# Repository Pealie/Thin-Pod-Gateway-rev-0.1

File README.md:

# Thin-Pod Gateway rev 0.1

<p align="left">
  
</p>
<p align="left">
  <strong>OSHWA Certified Open Source Hardware · UK000092</strong><br>
  Certified 16 July 2026 · <a href="https://certification.oshwa.org/uk000092.html">View certification record</a>
</p>

**Open-hardware carrier PCB for Thin-Pod UWB telemetry, host supervision and onward-networking experiments**

## Status at 16 July 2026

Thin-Pod Gateway rev 0.1 is certified by the Open Source Hardware Association under UID [`UK000092`](https://certification.oshwa.org/uk000092.html). The certified public baseline is the `v0.1` release, with post-certification status and directory references maintained on `main`.

The manufactured `rev 0.1f` carrier board has completed stable powered bring-up with the STM32 NUCLEO-N657X0-Q and Gateway-side DWM3001-CDK. The repository records:

- verified 5 V and 3.3 V distribution and common-ground continuity;
- corrected marginal DWM header solder joints affecting ground and RESET;
- valid RESET and READY rail levels;
- repeatable bidirectional NUCLEO-to-DWM `TPHIP GET_CAPABILITIES` exchange;
- physical DW3110 identity and initialisation on Gateway and Node DWM3001-CDKs;
- a matched 20-frame Gateway-to-Node UWB exchange;
- published KiCad project, schematic and PCB source for revision `0.1`;
- published Gerber, drill and fabrication ZIP outputs;
- clean schematic ERC and PCB DRC reports;
- recorded Gerber and drill inspection;
- recorded symbol and footprint provenance;
- a reconciled design-basis BOM with builder-selected compatible assembly hardware.

## Relationship to the certified Thin-Pod node

The companion [`Pealie/Thin-Pod-rev0.1`](https://github.com/Pealie/Thin-Pod-rev0.1) sensor-node carrier PCB is separately certified as OSHWA Open Source Hardware, UID [`UK000091`](https://certification.oshwa.org/uk000091.html), certified 28 May 2026.

The two certifications describe distinct hardware artefacts:

| Hardware artefact | OSHWA UID | Certification date |
|---|---|---|
| Thin-Pod rev 0.1 sensor-node carrier PCB | [`UK000091`](https://certification.oshwa.org/uk000091.html) | 28 May 2026 |
| Thin-Pod Gateway rev 0.1 carrier PCB | [`UK000092`](https://certification.oshwa.org/uk000092.html) | 16 July 2026 |

The node UID applies only to the sensor-node carrier PCB. The Gateway UID applies only to the Gateway carrier PCB and its declared certification package.

## Hardware scope

Thin-Pod Gateway rev 0.1 is a two-layer carrier PCB connecting:

| Reference | Module | Role |
|---|---|---|
| `U1` | STMicroelectronics `NUCLEO-N657X0-Q` | Main host and prospective analysis supervisor |
| `U2` | Qorvo `DWM3001-CDK` | Gateway-side UWB subsystem |
| `U3` | Seeed Studio `XIAO ESP32-C6` | Optional onward-networking subsystem |

The creator-controlled open-hardware contribution is the carrier PCB: power distribution, local decoupling, pull-ups, module interfaces, SPI/control routing, test access, mounting geometry, editable source and derived fabrication outputs.

The commercial modules remain third-party products whose internal designs are outside the Gateway open-hardware claim.

## Verified evidence

| Milestone | Result | Evidence |
|---|---|---|
| Stable carrier-board bring-up | PASS | [`docs/bringup/Gateway_rev0_1_Hardware_Bringup_Note.md`](docs/bringup/Gateway_rev0_1_Hardware_Bringup_Note.md) |
| NUCLEO-to-DWM physical host interface | PASS | [`docs/firmware/TPHIP_GET_CAPABILITIES_Physical_Validation.md`](docs/firmware/TPHIP_GET_CAPABILITIES_Physical_Validation.md) |
| DW3110 identity and initialisation | PASS | [`docs/validation/DW3110_Physical_Identity_Initialisation_Validation.md`](docs/validation/DW3110_Physical_Identity_Initialisation_Validation.md) |
| Matched 20-frame one-way RF exchange | PASS | [`docs/validation/DW3110_One_Way_RF_Exchange_Validation.md`](docs/validation/DW3110_One_Way_RF_Exchange_Validation.md) |
| Native KiCad source | PUBLISHED | [`hardware/source/README.md`](hardware/source/README.md) |
| Fabrication package and hashes | PUBLISHED | [`hardware/fabrication/RELEASE-MANIFEST.md`](hardware/fabrication/RELEASE-MANIFEST.md) |
| Schematic ERC | PASS | [`docs/validation/cad/rev0.1/Thin-Pod_Gateway_rev0.1_ERC.rpt`](docs/validation/cad/rev0.1/Thin-Pod_Gateway_rev0.1_ERC.rpt) |
| PCB DRC | PASS | [`docs/validation/cad/rev0.1/Thin-Pod_Gateway_rev0.1_DRC.rpt`](docs/validation/cad/rev0.1/Thin-Pod_Gateway_rev0.1_DRC.rpt) |
| Gerber and drill inspection | PASS | [`docs/validation/cad/rev0.1/Gerber_Drill_Inspection_Record.md`](docs/validation/cad/rev0.1/Gerber_Drill_Inspection_Record.md) |
| Symbol and footprint provenance | RECORDED | [`docs/footprint-provenance.md`](docs/footprint-provenance.md) |
| Assembly BOM | RECONCILED | [`hardware/bom/Thin-Pod_Gateway_rev0.1_BOM.md`](hardware/bom/Thin-Pod_Gateway_rev0.1_BOM.md) |

## Design and fabrication identity

The manufactured board may carry `rev 0.1f`. This is retained as the physical fabrication-build identity within the certified Thin-Pod Gateway rev 0.1 release record.

Published native source:

```text
hardware/source/kicad/rev0.1/
```

Published manufacturing outputs:

```text
hardware/fabrication/rev0.1/
```

The release Gerber job records project revision `0.1`. The regenerated outputs preserve the intended electrical connectivity, board outline, mounting geometry, module-interface positions, test-point arrangement and layer content of the manufactured rev 0.1f carrier.

## Assembly interface treatment

Builder-selected pin headers and/or socket strips compatible with the NUCLEO-N657X0-Q ST Morpho interfaces, DWM3001-CDK J10 interface, and optional XIAO ESP32-C6 carrier footprint are suitable for assembly. Header brand, plating, socket style and standoff selection are assembly choices outside the carrier-PCB certification scope.

## Licences

| Material | Licence |
|---|---|
| Creator-designed hardware source and derived fabrication outputs | `CERN-OHL-W-2.0` |
| Project-authored firmware, scripts and software examples | `MIT` |
| Creator-authored documentation and owned images | `CC-BY-4.0` |
| Third-party modules, software and CAD | Original applicable terms |

These are the licence selections recorded for OSHWA certification UID `UK000092`.

See [`LICENSE.md`](LICENSE.md), [`LICENSE-HARDWARE.md`](LICENSE-HARDWARE.md), [`LICENSE-SOFTWARE.md`](LICENSE-SOFTWARE.md), [`LICENSE-DOCUMENTATION.md`](LICENSE-DOCUMENTATION.md), [`THIRD_PARTY_NOTICES.md`](THIRD_PARTY_NOTICES.md) and [`docs/footprint-provenance.md`](docs/footprint-provenance.md).

## OSHWA certification record

| Item | Record |
|---|---|
| Project | Thin-Pod Gateway |
| Hardware release | rev 0.1 |
| OSHWA UID | [`UK000092`](https://certification.oshwa.org/uk000092.html) |
| Certification date | 16 July 2026 |
| Canonical release tag | `v0.1` |
| Public application record | [`oshwa/application-record.md`](oshwa/application-record.md) |
| Certification scope | [`docs/certification-scope.md`](docs/certification-scope.md) |
| Certification completion checklist | [`docs/oshwa/Gateway_OSHWA_Preparation_Checklist.md`](docs/oshwa/Gateway_OSHWA_Preparation_Checklist.md) |

The OSHWA certification confirms the declared open-source hardware, software and documentation licensing position. It does not constitute EMC, radio, electrical-safety, CE, UKCA, industrial-performance or product-safety approval.

## Current limitations

The release does not claim Node-to-Gateway vibration-window transport, ranging, field-qualified RF performance, calibrated transmit power, antenna/coexistence performance, authenticated radio records, secure boot enforcement, production OTA, Gateway DSP/TinyML performance, EMC, radio, electrical-safety, CE or UKCA compliance.

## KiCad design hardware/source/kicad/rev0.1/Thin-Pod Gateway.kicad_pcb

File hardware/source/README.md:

# Editable hardware source

This directory contains the preferred modifiable source for Thin-Pod Gateway rev 0.1.

## Published KiCad project

The release source is stored at:

```text
hardware/source/kicad/rev0.1/
├── Thin-Pod Gateway.kicad_pro
├── Thin-Pod Gateway.kicad_sch
└── Thin-Pod Gateway.kicad_pcb
```

The schematic and PCB title blocks identify the design revision as `0.1`. The KiCad project and PCB fabrication-output paths use the repository-relative location:

```text
../../../fabrication/rev0.1/
```

This removes the private Windows/OneDrive path that was present in the working project before publication. No schematic connectivity, component placement, routing or board geometry was intentionally changed by that portability correction.

## Source status

The native KiCad source and corresponding Gerber/drill release package were committed on 13 July 2026. The earlier missing-source publication gate is therefore cleared.

The remaining release-verification work is:

1. open the project in a clean KiCad 10 environment;
2. confirm that no unavailable private symbol or footprint library is required;
3. run schematic ERC and PCB DRC;
4. inspect the generated Gerbers and drill data in a Gerber viewer;
5. record symbol and footprint provenance;
6. reconcile the fitted BOM and module-header/socket choices;
7. freeze the validated source and fabrication package under a public release tag.

The editable KiCad project is the normative design source. Gerbers, drill data and the fabrication ZIP are derived convenience outputs.

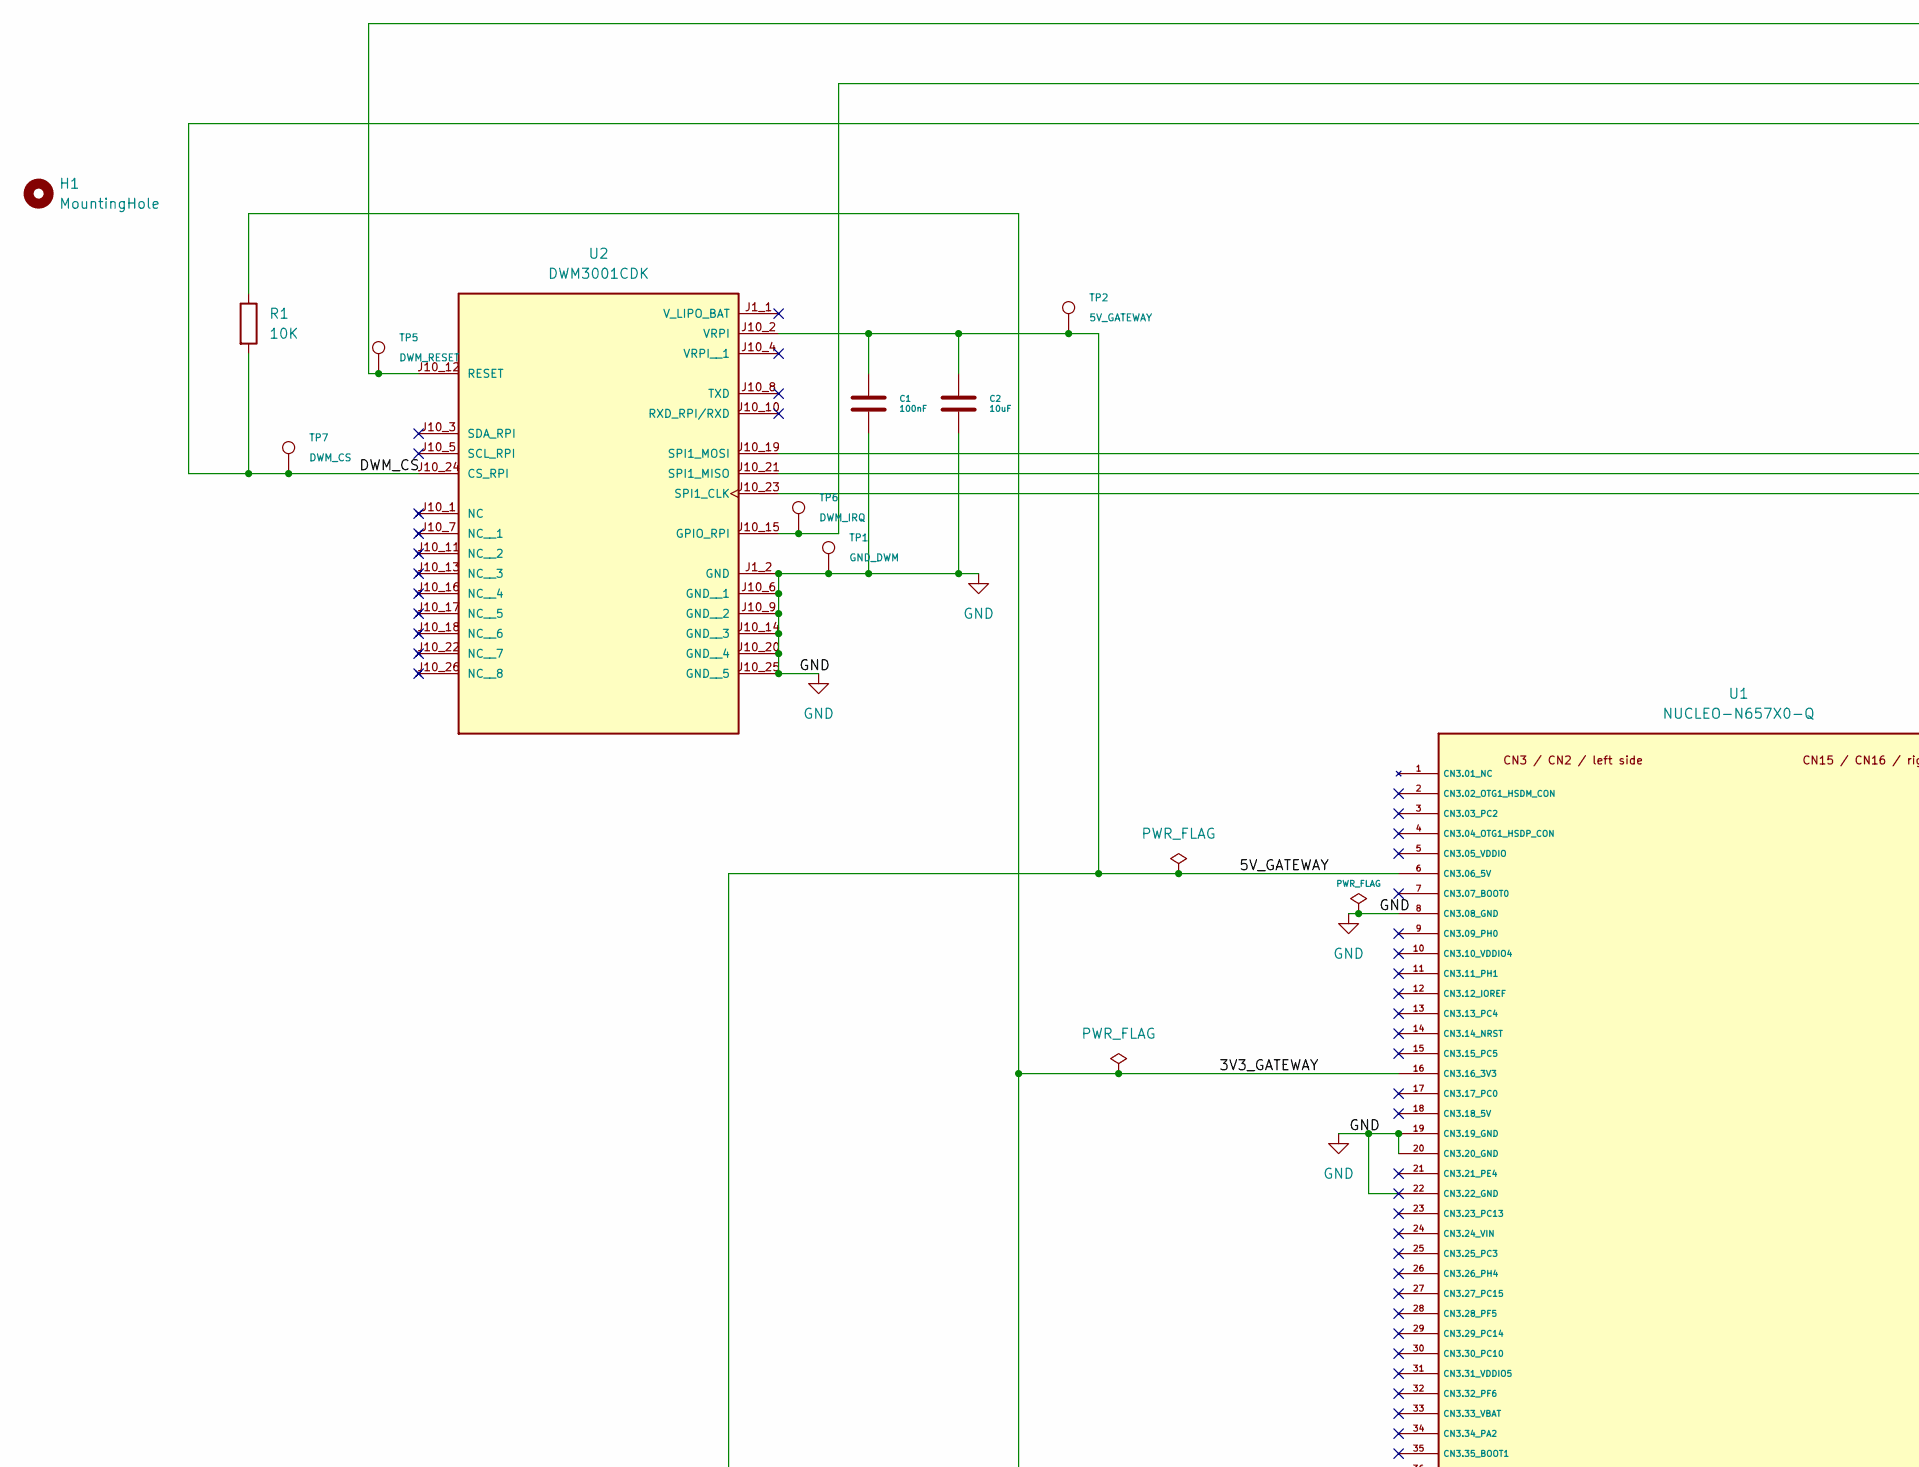
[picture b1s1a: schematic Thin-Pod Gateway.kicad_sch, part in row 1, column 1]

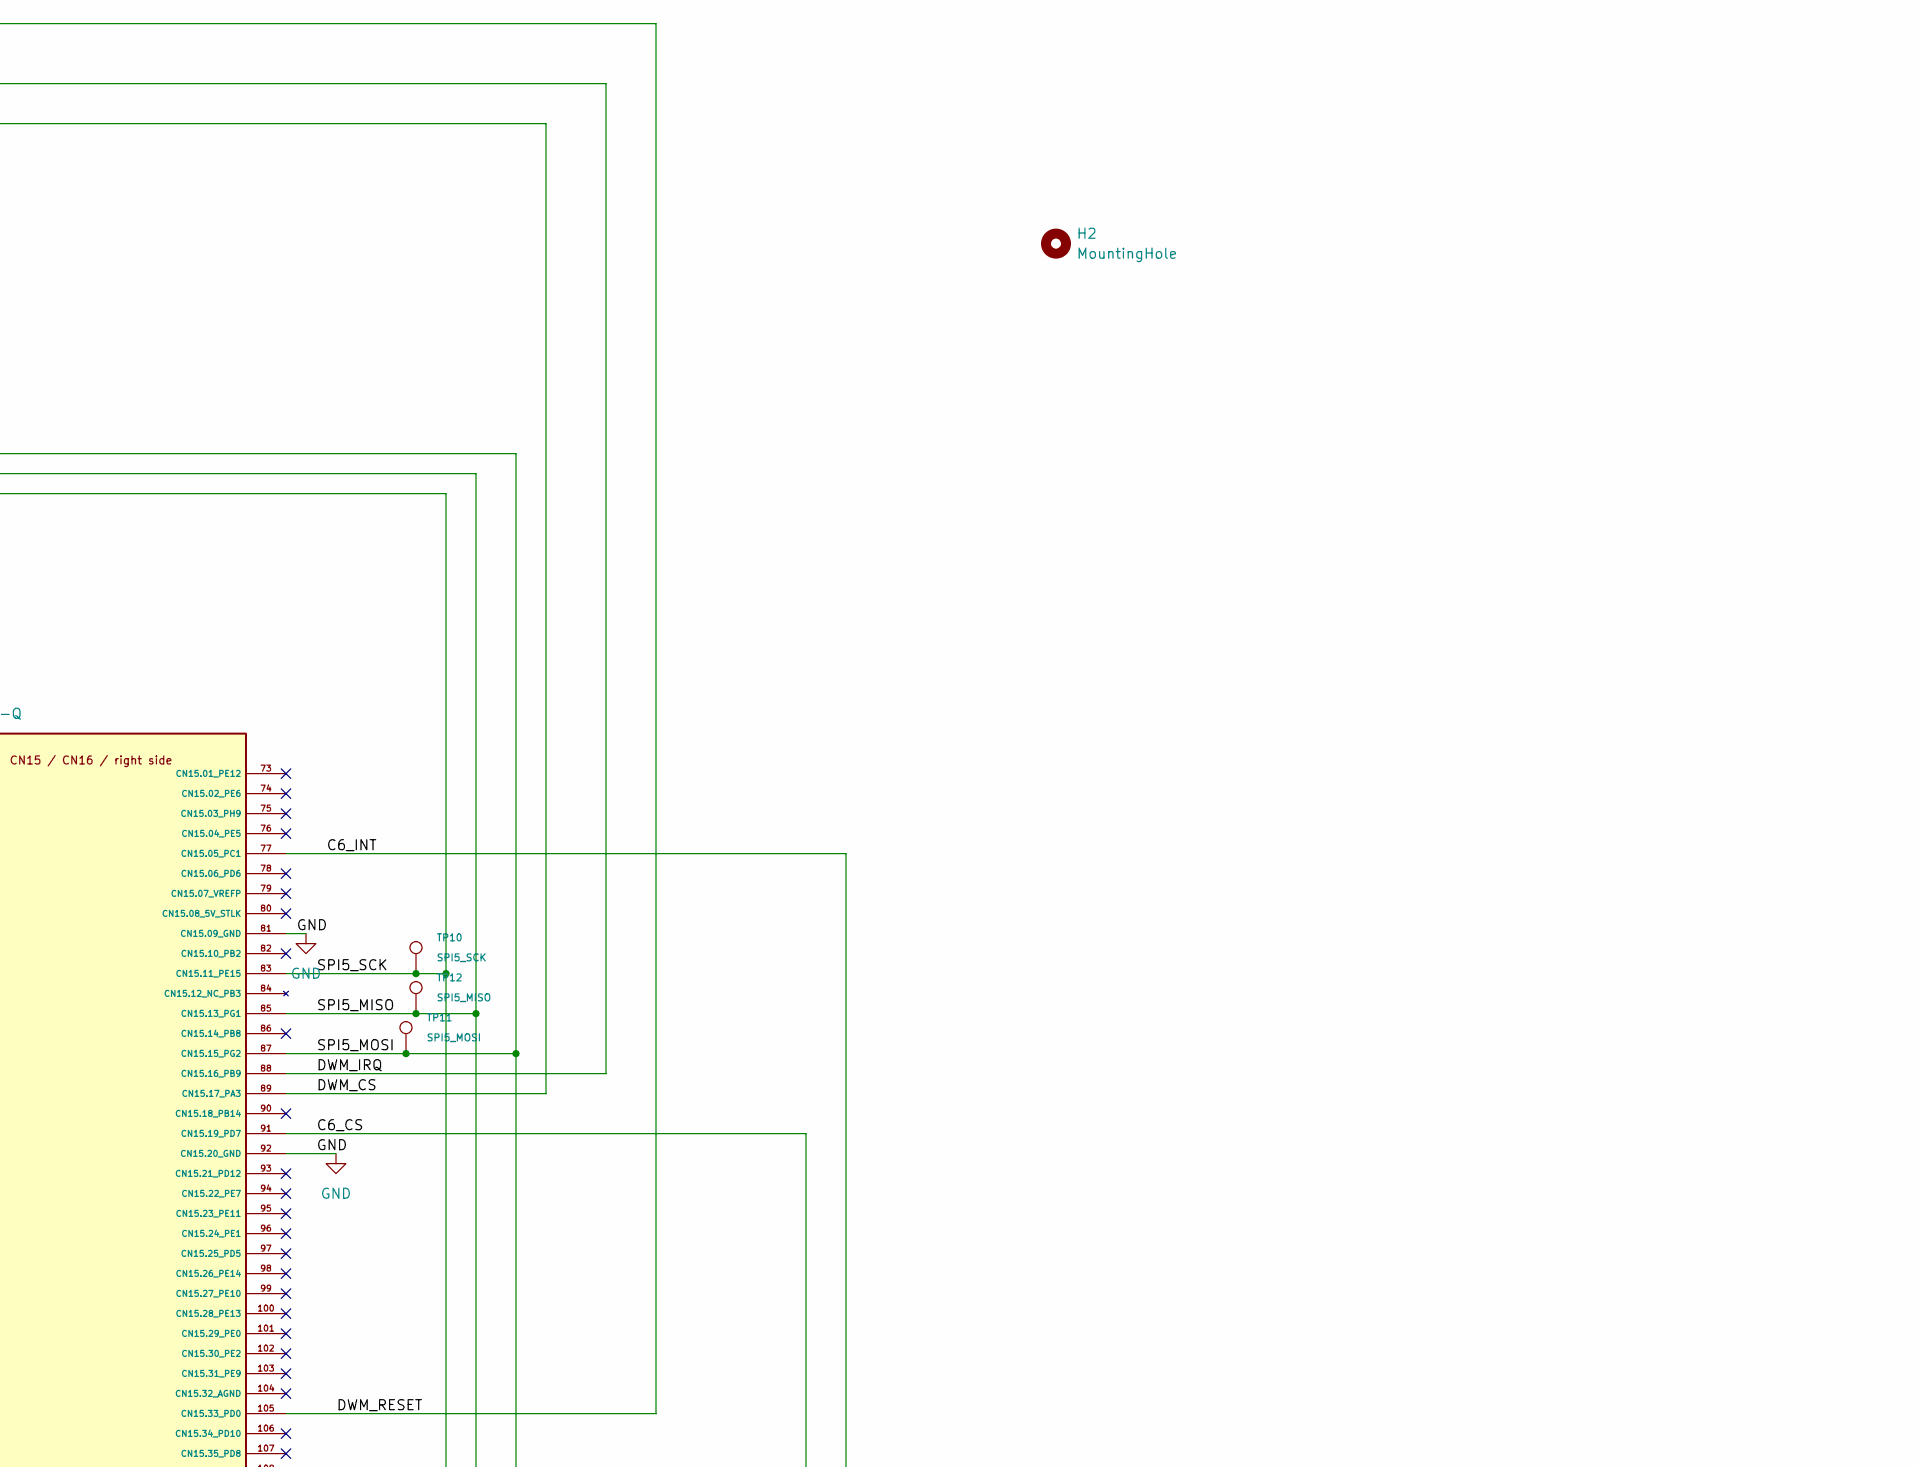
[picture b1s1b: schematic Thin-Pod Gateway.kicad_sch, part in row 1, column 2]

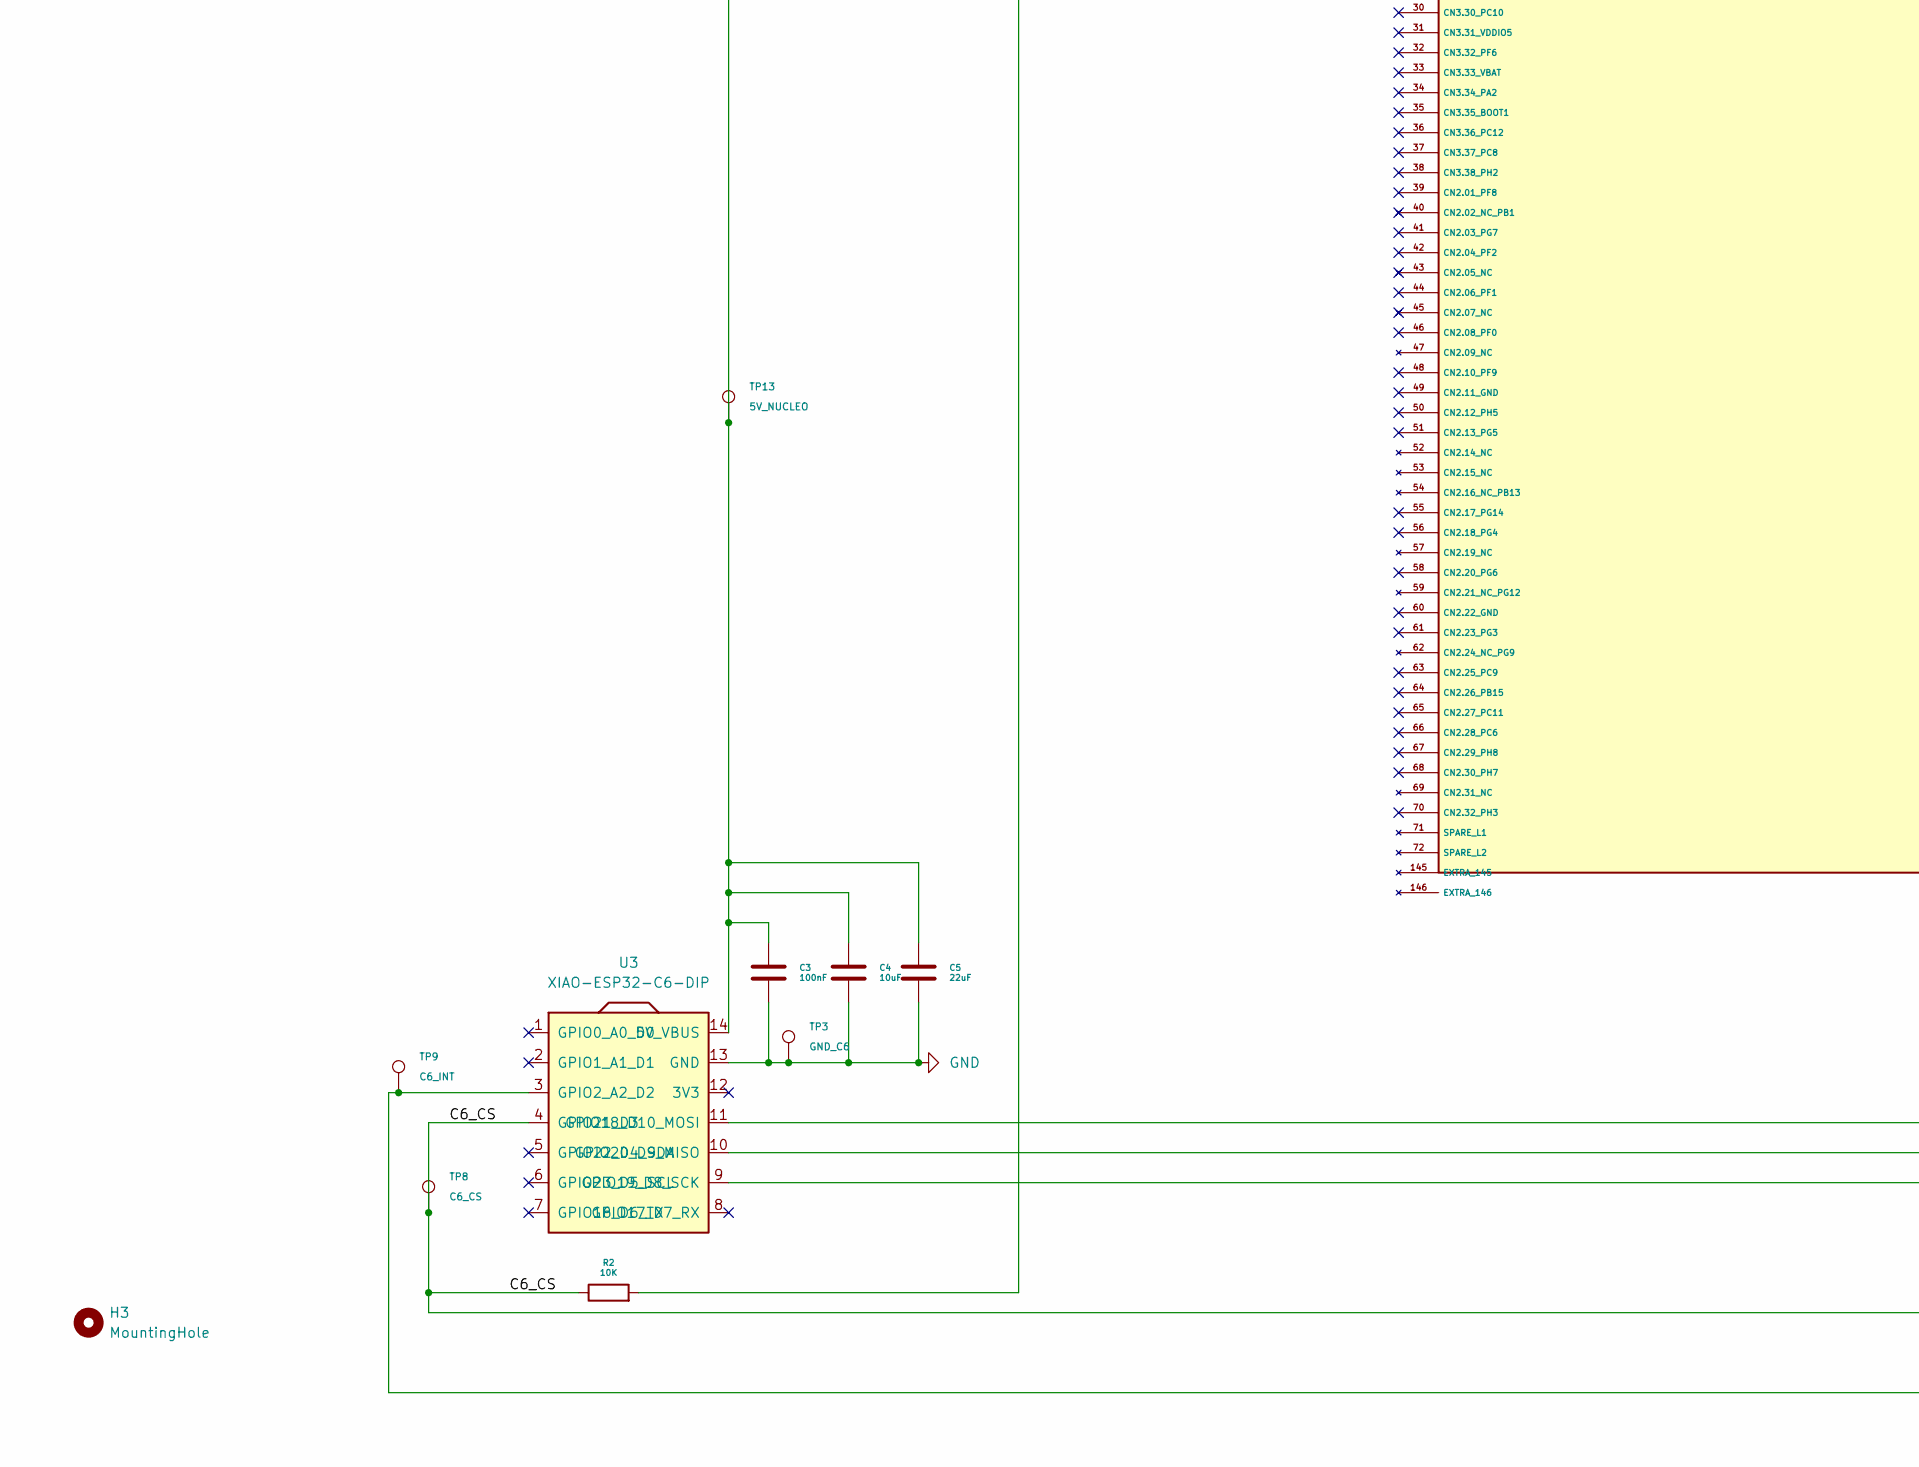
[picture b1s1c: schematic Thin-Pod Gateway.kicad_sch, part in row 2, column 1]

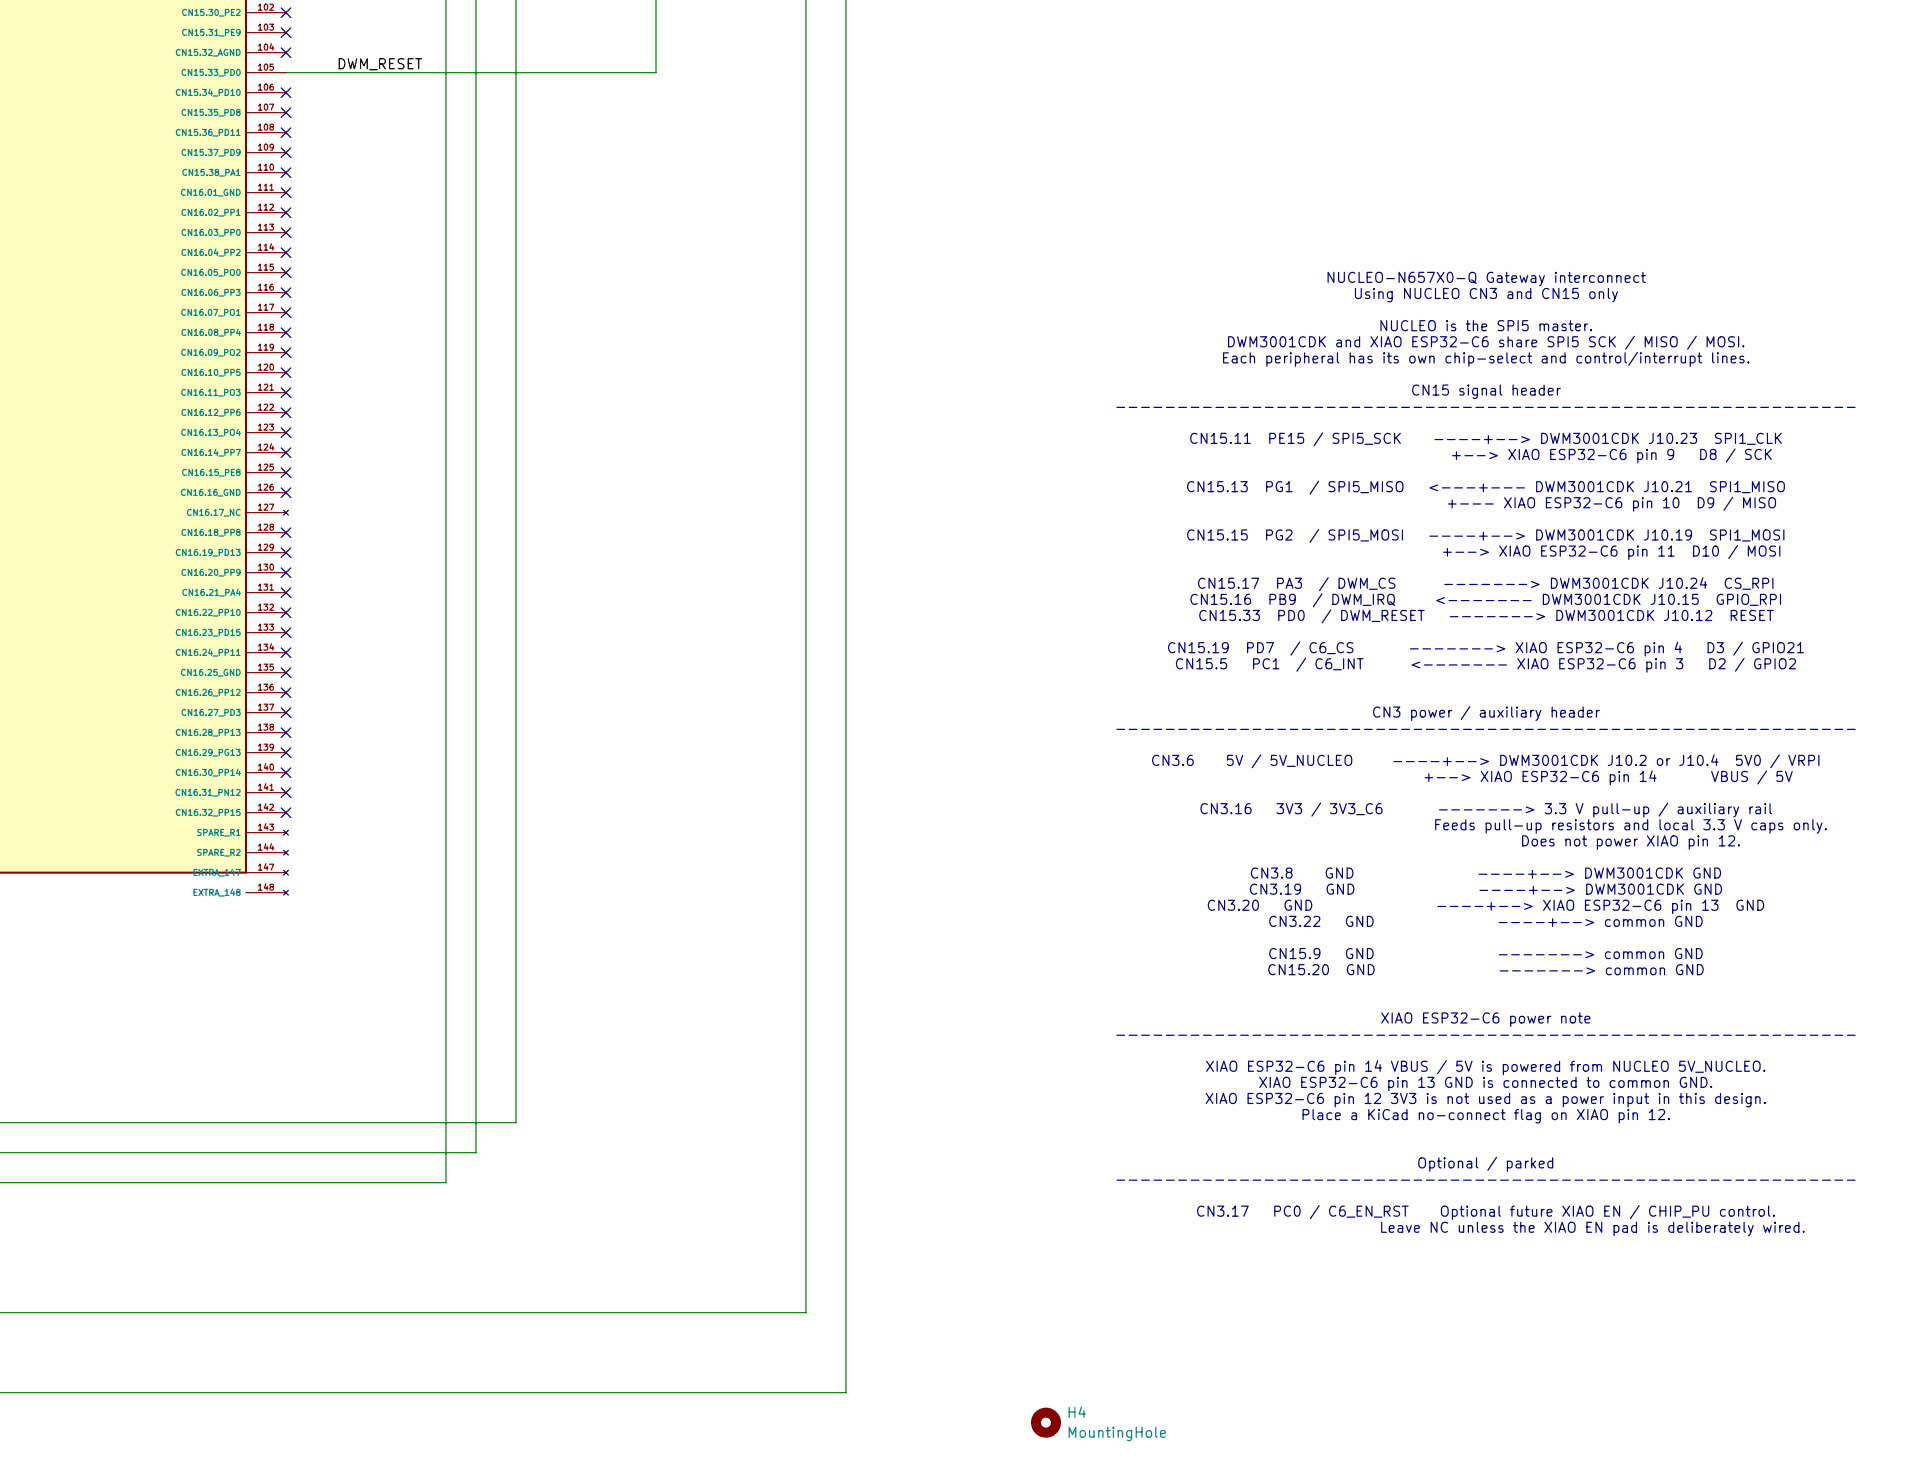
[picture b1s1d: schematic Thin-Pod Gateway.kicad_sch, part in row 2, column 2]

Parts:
C1, C3: 100nF; C_Disc_D5.0mm_W2.5mm_P5.00mm
C2, C4: 10uF; C_Disc_D5.0mm_W2.5mm_P5.00mm
C5: 22uF; C_Disc_D5.0mm_W2.5mm_P5.00mm
H1, H2, H3, H4: MountingHole; MountingHole_3.2mm_M3
R1, R2: 10K; R_Axial_DIN0207_L6.3mm_D2.5mm_P7.62mm_Horizontal
TP1: GND_DWM; TestPoint_THTPad_1.5x1.5mm_Drill0.7mm
TP2: 5V_GATEWAY; TestPoint_THTPad_1.5x1.5mm_Drill0.7mm
TP3: GND_C6; TestPoint_THTPad_1.5x1.5mm_Drill0.7mm
TP5: DWM_RESET; TestPoint_THTPad_1.5x1.5mm_Drill0.7mm
TP6: DWM_IRQ; TestPoint_THTPad_1.5x1.5mm_Drill0.7mm
TP7: DWM_CS; TestPoint_THTPad_1.5x1.5mm_Drill0.7mm
TP8: C6_CS; TestPoint_THTPad_1.5x1.5mm_Drill0.7mm
TP9: C6_INT; TestPoint_THTPad_1.5x1.5mm_Drill0.7mm
TP10: SPI5_SCK; TestPoint_THTPad_2.0x2.0mm_Drill1.0mm
TP11: SPI5_MOSI; TestPoint_THTPad_2.0x2.0mm_Drill1.0mm
TP12: SPI5_MISO; TestPoint_THTPad_2.0x2.0mm_Drill1.0mm
TP13: 5V_NUCLEO; TestPoint_THTPad_1.5x1.5mm_Drill0.7mm
U1: NUCLEO-N657X0-Q; NUCLEO-N657X0-Q_Nucleo144_STMorpho_STLink_MountingHoles
U2: DWM3001CDK; MODULE_DWM3001CDK; PARTREV B
U3: XIAO-ESP32-C6-DIP

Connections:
/3V3_GATEWAY: R1.1, R2.2, U1.16 (CN3.16_3V3); also elsewhere on the board
/5V_GATEWAY: C1.1, C2.1, C3.1, C4.1, C5.1, TP2.1 (1_1), TP13.1 (1_1), U1.6 (CN3.06_5V), U2.J10_2 (VRPI), U3.14 (5V_VBUS)
/C6_CS: R2.1, TP8.1 (1_1), U1.91 (CN15.19_PD7), U3.4 (GPIO21_D3)
/C6_INT: TP9.1 (1_1), U1.77 (CN15.05_PC1), U3.3 (GPIO2_A2_D2)
/DWM_CS: R1.2, TP7.1 (1_1), U1.89 (CN15.17_PA3), U2.J10_24 (CS_RPI)
/DWM_IRQ: TP6.1 (1_1), U1.88 (CN15.16_PB9), U2.J10_15 (GPIO_RPI)
/DWM_RESET: TP5.1 (1_1), U1.105 (CN15.33_PD0), U2.J10_12 (RESET)
/SPI5_MISO: TP12.1 (1_1), U1.85 (CN15.13_PG1), U2.J10_21 (SPI1_MISO), U3.10 (GPIO20_D9_MISO)
/SPI5_MOSI: TP11.1 (1_1), U1.87 (CN15.15_PG2), U2.J10_19 (SPI1_MOSI), U3.11 (GPIO18_D10_MOSI)
/SPI5_SCK: TP10.1 (1_1), U1.83 (CN15.11_PE15), U2.J10_23 (SPI1_CLK), U3.9 (GPIO19_D8_SCK)
GND: C1.2, C2.2, C3.2, C4.2, C5.2, TP1.1 (1_1), TP3.1 (1_1), U1.1 (CN3.01_NC), U1.2 (CN3.02_OTG1_HSDM_CON), U1.8 (CN3.08_GND), U1.19 (CN3.19_GND), U1.20 (CN3.20_GND), U1.22 (CN3.22_GND), U1.71 (SPARE_L1), U1.72 (SPARE_L2), U1.73 (CN15.01_PE12), U1.74 (CN15.02_PE6), U1.81 (CN15.09_GND), U1.92 (CN15.20_GND), U1.143 (SPARE_R1), U1.144 (SPARE_R2), U2.J1_2 (GND), U2.J10_6 (GND__1), U2.J10_9 (GND__2), U2.J10_14 (GND__3), U2.J10_20 (GND__4), U2.J10_25 (GND__5), U3.13 (GND)

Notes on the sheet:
NUCLEO-N657X0-Q Gateway interconnect Using NUCLEO CN3 and CN15 only NUCLEO is the SPI5 master. DWM3001CDK and XIAO ESP32-C6 share SPI5 SCK / MISO / MOSI. Each peripheral has its own chip-select and control/interrupt lines. CN15 signal header ---------------------------------------------------------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

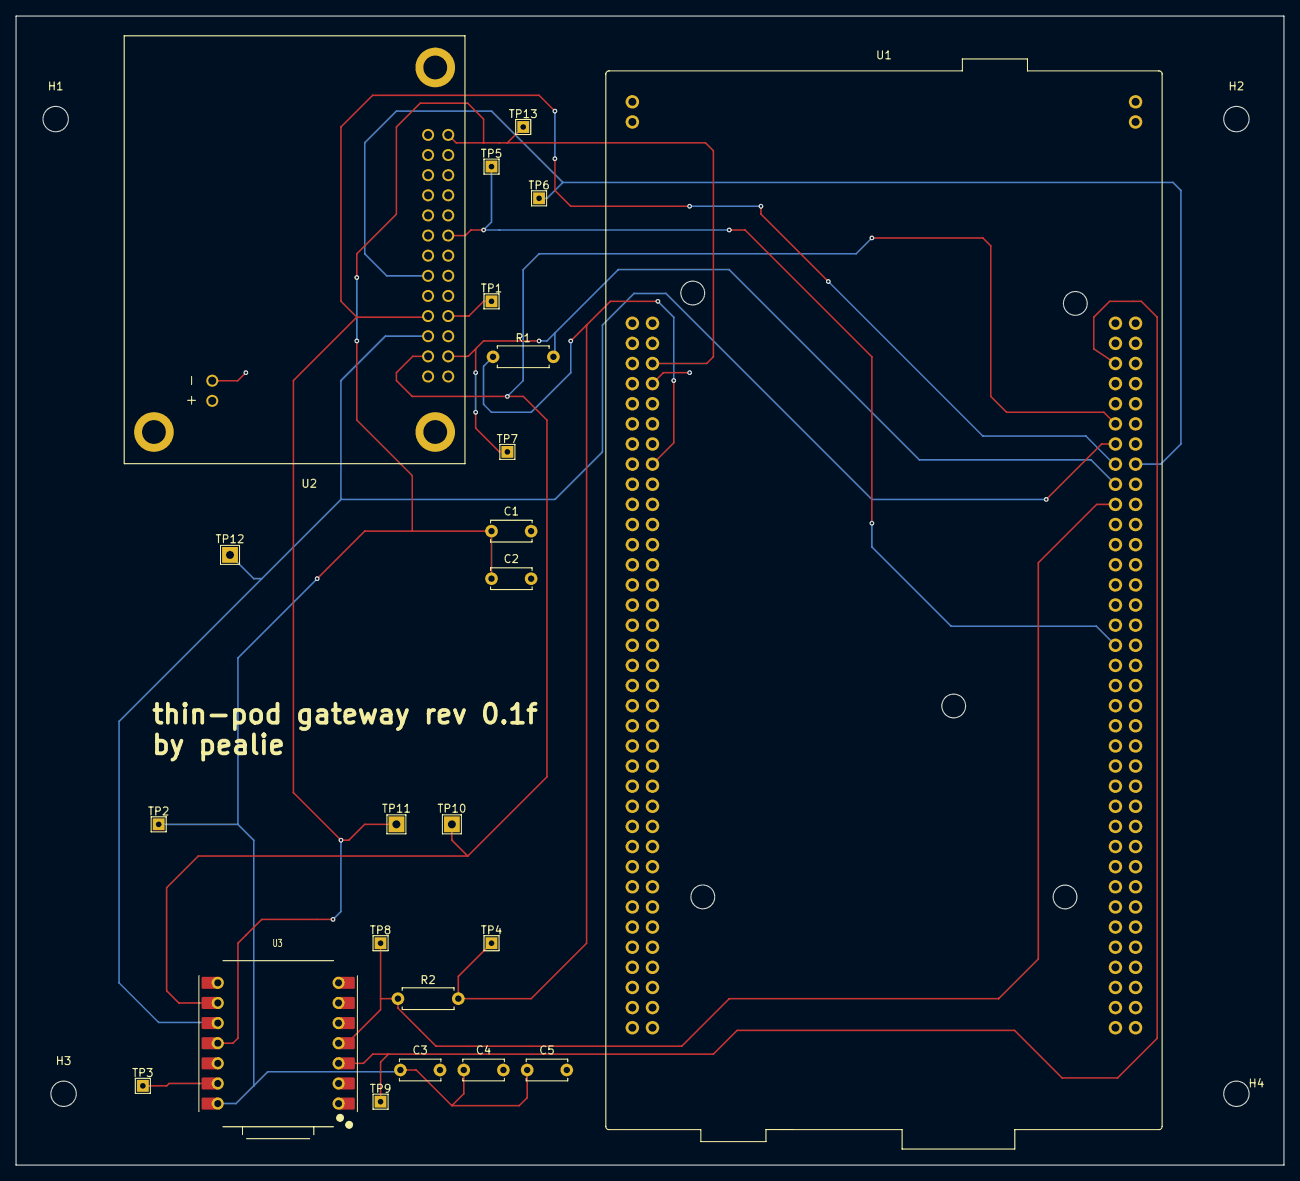
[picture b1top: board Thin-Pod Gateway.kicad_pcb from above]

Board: 2 copper layers, 160.0 x 145.0 mm, 27 parts (0 on the bottom side), 11 nets.

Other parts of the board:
TP4: 3V3_GATEWAY; TestPoint_THTPad_1.5x1.5mm_Drill0.7mm

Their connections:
/3V3_GATEWAY: TP4.1 (1_1); also elsewhere on the board

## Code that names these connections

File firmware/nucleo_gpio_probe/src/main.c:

#include <errno.h>
#include <stdint.h>

#include <zephyr/device.h>
#include <zephyr/drivers/gpio.h>
#include <zephyr/kernel.h>
#include <zephyr/sys/printk.h>

#define PROBE_SLEEP_MS 1000
#define TOGGLE_HOLD_MS 250

static const struct gpio_dt_spec dwm_reset =
	GPIO_DT_SPEC_GET(DT_ALIAS(dwm_reset), gpios);

static const struct gpio_dt_spec dwm_cs =
	GPIO_DT_SPEC_GET(DT_ALIAS(dwm_cs), gpios);

static const struct gpio_dt_spec dwm_irq =
	GPIO_DT_SPEC_GET(DT_ALIAS(dwm_irq), gpios);

static int check_gpio_ready(const struct gpio_dt_spec *spec, const char *name)
{
	if (!device_is_ready(spec->port)) {
		printk("ERROR: %s GPIO device not ready\n", name);
		return -ENODEV;
	}

	printk("%s ready: controller=%s pin=%u\n",
	       name, spec->port->name, spec->pin);

	return 0;
}

int main(void)
{
	int irq_level;
	uint32_t heartbeat = 0U;

	printk("\nThin-Pod Gateway rev0.1 NUCLEO GPIO probe\n");
	printk("Board: nucleo_n657x0_q\n");
	printk("Purpose: RESET / CS / IRQ pin-path confirmation only\n");
	printk("No SPI. No DW3110 register access. No UWB RF.\n\n");

	if (check_gpio_ready(&dwm_reset, "DWM_RESET / PD0") != 0) {
		return 0;
	}

	if (check_gpio_ready(&dwm_cs, "DWM_CS / PA3") != 0) {
		return 0;
	}

	if (check_gpio_ready(&dwm_irq, "DWM_IRQ / PB9") != 0) {
		return 0;
	}

	if (gpio_pin_configure_dt(&dwm_reset, GPIO_OUTPUT_LOW) != 0) {
		printk("ERROR: failed to configure DWM_RESET / PD0\n");
		return 0;
	}

	if (gpio_pin_configure_dt(&dwm_cs, GPIO_OUTPUT_LOW) != 0) {
		printk("ERROR: failed to configure DWM_CS / PA3\n");
		return 0;
	}

	if (gpio_pin_configure_dt(&dwm_irq, GPIO_INPUT) != 0) {
		printk("ERROR: failed to configure DWM_IRQ / PB9\n");
		return 0;
	}

	printk("GPIO configuration complete\n");
	printk("Probe pattern: RESET and CS toggle low/high; IRQ is sampled\n\n");

	while (1) {
		gpio_pin_set_raw(dwm_reset.port, dwm_reset.pin, 0);
		gpio_pin_set_raw(dwm_cs.port, dwm_cs.pin, 0);
		k_msleep(TOGGLE_HOLD_MS);

		irq_level = gpio_pin_get_raw(dwm_irq.port, dwm_irq.pin);
		printk("probe=%u phase=LOW reset=0 cs=0 irq=%d\n",
		       heartbeat, irq_level);

		gpio_pin_set_raw(dwm_reset.port, dwm_reset.pin, 1);
		gpio_pin_set_raw(dwm_cs.port, dwm_cs.pin, 1);
		k_msleep(TOGGLE_HOLD_MS);

		irq_level = gpio_pin_get_raw(dwm_irq.port, dwm_irq.pin);
		printk("probe=%u phase=HIGH reset=1 cs=1 irq=%d\n",
		       heartbeat, irq_level);

		heartbeat++;
		k_msleep(PROBE_SLEEP_MS);
	}

	return 0;
}

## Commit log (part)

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2026-06-15 Add Zephyr RTT alive-test firmware baseline
2026-06-15 Add staged UWB responder and initiator firmware harness
2026-06-15 Clean escaped underscores in README paths
2026-06-16 Add engineering log 85 for Stage-1 firmware bring-up
2026-06-16 Create Stage-2 UWB RF proof firmware scaffolds
2026-06-16 Add Stage-2 UWB RF proof notes
2026-06-17 Document Zephyr DW3110 Stage-2 RF bring-up plan
2026-06-17 Document NUCLEO SPI5 Gateway PCB pin mapping
2026-06-17 Document NUCLEO SPI5 GPIO probe app plan
2026-06-18 Document Gateway module substitution and EOL strategy
2026-06-18 Add post-Gateway roadmap synthesis
2026-06-18 Refine post-Gateway roadmap framing
2026-06-27 Archive non-completion Gateway planning documents
2026-06-27 Document Gateway rev 0.1 hardware bring-up note
2026-06-27 Mark Gateway rev 0.1 pin map for final verification
2026-06-27 Add minimal Gateway SPI GPIO probe app scaffold
2026-06-27 Define Gateway telemetry packet v1
2026-06-27 Add Gateway telemetry packet parser
2026-06-27 Add Gateway release artifact check script
2026-06-27 Ignore Python cache files
2026-06-27 Add Gateway rev 0.1 validation log
2026-06-27 Add Gateway GitHub Actions artifact check
2026-06-27 Add Gateway OSHWA preparation checklist
2026-06-28 Evaluate Memfault nRF Cloud observability fit
2026-06-28 Add Memfault nRF Cloud PR notes
2026-06-28 Add Gateway PCB and node images
2026-06-28 Reference Gateway hardware images in README
2026-06-28 Add engineering log 88 for Gateway weekend work
2026-06-28 Update engineering log 88 after PR merge
2026-06-30 Add engineering log 89 for Gateway branch consolidation
